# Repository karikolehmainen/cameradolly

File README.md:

# Camera Timelapse Dolly #
This camera dolly was born from desire to take moving timelapse videos in cold 
environment. Project has not evolved in features much since its conception 
during 2016 but in implementation much so. First implementation was using Adafruit
Motor HAT with NEMA17 stepper motors to move dolly and rotate camera head. Only new
feature is autamtec head alignment according to earth axis that has appeared 
since the first version. This is noe third revision. 
## Features ##
Summary of main high level features of the dolly
- Move camera along rail using timing belt
- End stops to detect end of rail
- Rotate camera 360° 
- Provide 8V power for camera (necessary in freezing conditions)
- Have lens heating element with temperature sensor
- Align camera rotation axis with earth axis for star tracking
- Control camera via USB interface
- Mobile app controls and 3G/4G connectivity

## Changes and rationale ##
Major change has been to ditch stepper motors in favour of DC motors. Main reason
behind the change was to enable star tracking and loooong exposures (like minutes
not seconds) as well as preserve energy. 
Also full size raspberry pi has been changes to Zero for more compact construction
and slightly less power consumption. Main drawback of this is the loss of 4G 
connectivity.

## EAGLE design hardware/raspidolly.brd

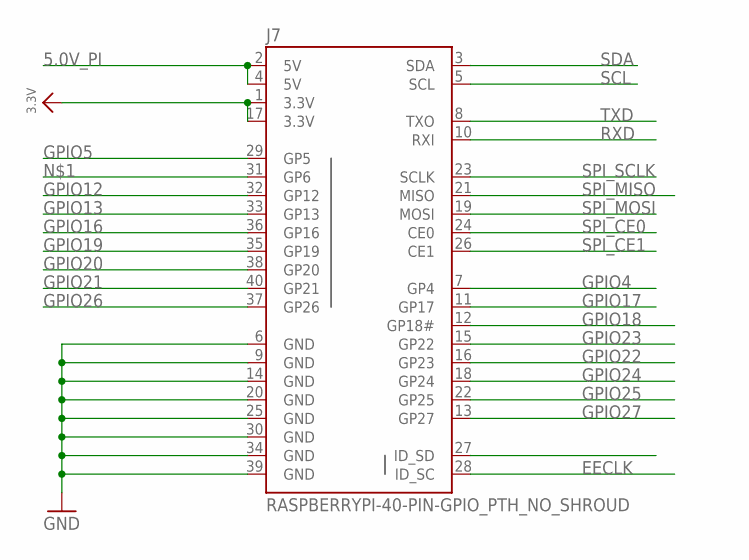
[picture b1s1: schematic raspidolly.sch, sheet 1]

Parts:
J7: RASPBERRYPI-40-PIN-GPIO_PTH_NO_SHROUD; 2X20

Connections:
3.3V: J7.1 (3.3V), J7.17 (3.3V); also elsewhere on the board
5.0V_PI: J7.2 (5V), J7.4 (5V); also elsewhere on the board
EECLK: J7.28 (ID_SC)
EEDATA: J7.27 (ID_SD)
GND: J7.6 (GND), J7.9 (GND), J7.14 (GND), J7.20 (GND), J7.25 (GND), J7.30 (GND), J7.34 (GND), J7.39 (GND); also elsewhere on the board
GPIO4: J7.7 (GP4); also elsewhere on the board
GPIO5: J7.29 (GP5)
GPIO12: J7.32 (GP12); also elsewhere on the board
GPIO13: J7.33 (GP13); also elsewhere on the board
GPIO16: J7.36 (GP16); also elsewhere on the board
GPIO17: J7.11 (GP17); also elsewhere on the board
GPIO18: J7.12 (GP18#); also elsewhere on the board
GPIO19: J7.35 (GP19); also elsewhere on the board
GPIO20: J7.38 (GP20); also elsewhere on the board
GPIO21: J7.40 (GP21); also elsewhere on the board
GPIO22: J7.15 (GP22)
GPIO23: J7.16 (GP23)
GPIO24: J7.18 (GP24)
GPIO25: J7.22 (GP25); also elsewhere on the board
GPIO26: J7.37 (GP26); also elsewhere on the board
GPIO27: J7.13 (GP27); also elsewhere on the board
RXD: J7.10 (RXI); also elsewhere on the board
SCL: J7.5 (SCL); also elsewhere on the board
SDA: J7.3 (SDA); also elsewhere on the board
SPI_CE0: J7.24 (CE0)
SPI_CE1: J7.26 (CE1)
SPI_MISO: J7.21 (MISO)
SPI_MOSI: J7.19 (MOSI)
SPI_SCLK: J7.23 (SCLK)
TXD: J7.8 (TXO); also elsewhere on the board

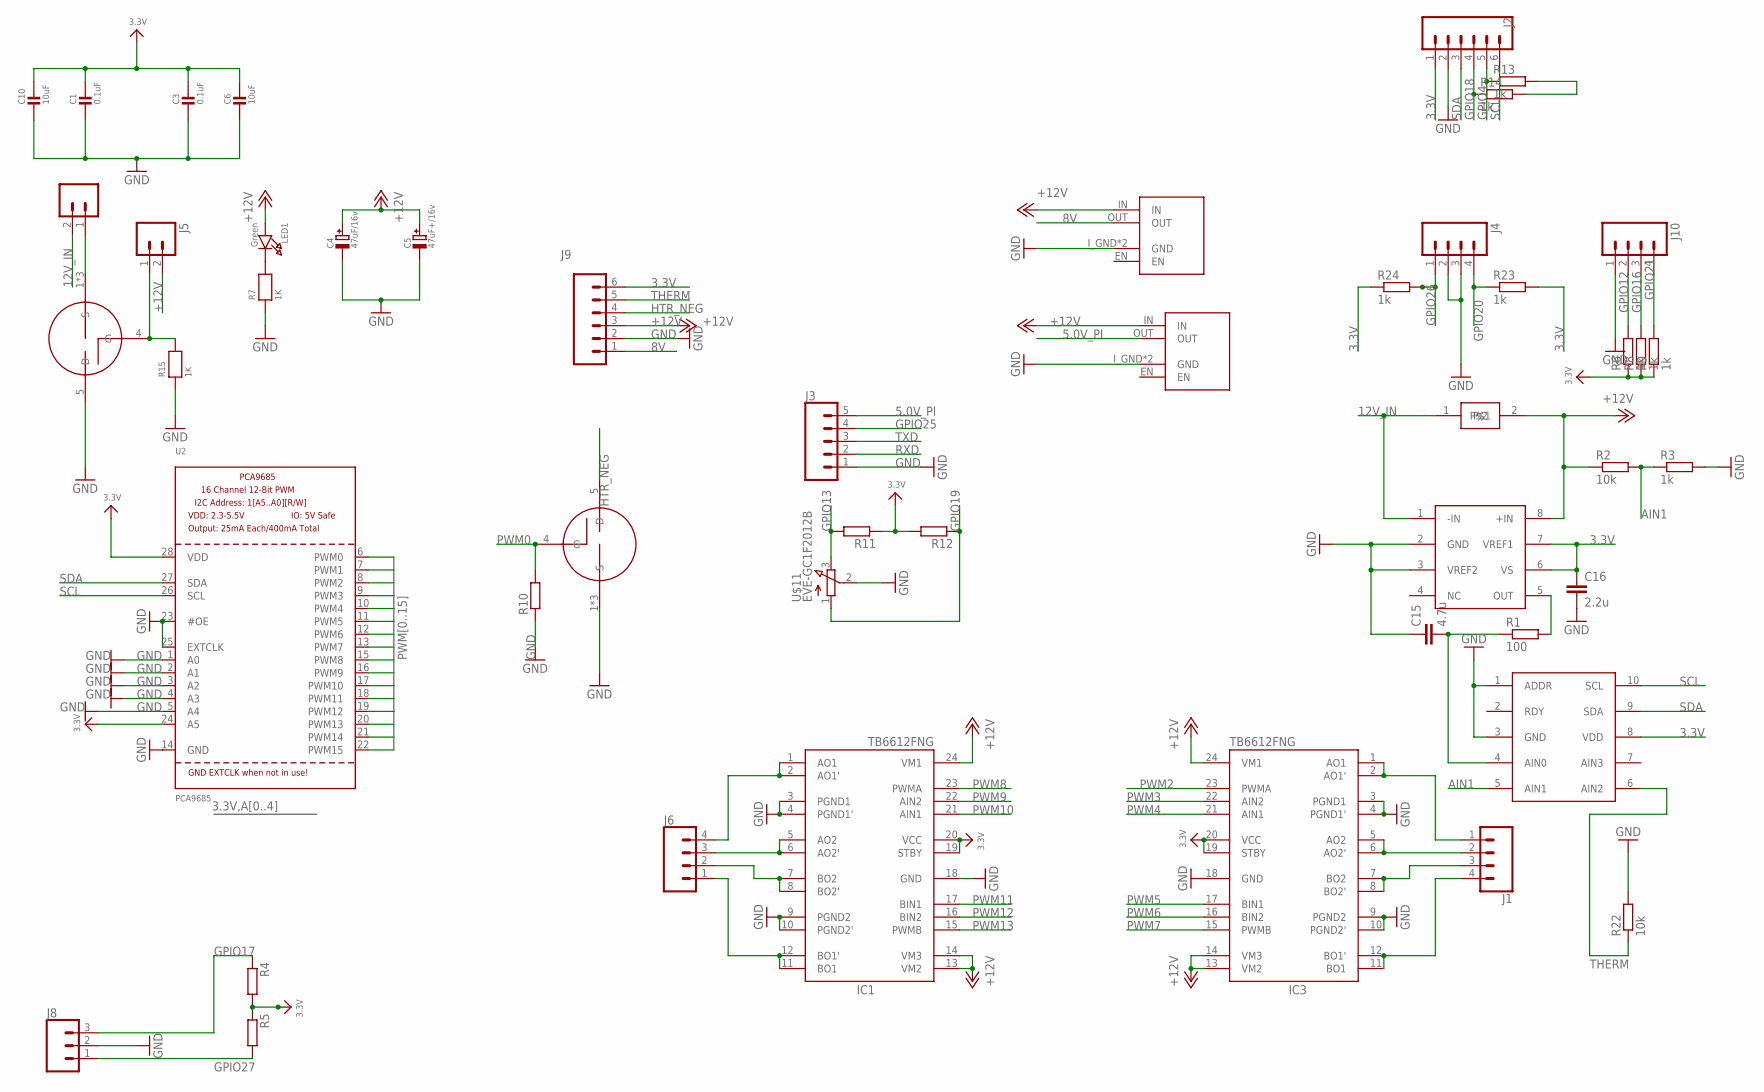
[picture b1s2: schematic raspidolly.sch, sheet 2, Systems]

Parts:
C1, C3: 0.1uF; 0805-NO
C4: 47uF/16v; PANASONIC_C
C5: 47uF+/16v; PANASONIC_C
C6, C10: 10uF; 0805-NO
C15: 4.7u; C0805
C16: 2.2u; C0805
IC1, IC3: TB6612FNG; SSOP24
J1, J6: CONN_04; 1X04
J2, J9: CONN_061.27MM; 1X06_1.27MM
J3: CONN_051.27MM; 1X05_1.27MM
J4, J10: M04JST; 1X04-1.5MM_JST
J5: M02PTH; 1X02
J8: CONN_03JST-PTH-VERT; JST-3-PTH-VERT
LED1: Green; CHIPLED_0805_NOOUTLINE
MPOWER: CONN_02; 1X02
R1: 100; R0805
R2, R22: 10k; R0805
R3, R6, R8, R9, R13, R14, R23, R24: 1k; R0805
R4, R5, R10, R11, R12: R-EU_R0805; R0805
R7, R15: 1K; 0805-NO
U2: PCA9685; TSSOP28
U$5, U$6: BUK9M; LFPAK33
U$8, U$10: UFH-BUCK
U$11: EVE-GC1F2012B; EVE
U$14: AD8418; MSOP08
U$15: ADS1015; VSSOP10
U$17: RESISTOR; 3921

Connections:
3.3V: C1.1, C3.1, C6.1, C10.1, C16.1, IC1.19 (STBY), IC1.20 (VCC), IC3.19 (STBY), IC3.20 (VCC), J2.1, J9.6, R4.2, R5.1, R6.1, R8.1, R9.1, R11.1, R12.2, R13.2, R14.2, R23.2, R24.1, U2.24 (A5), U2.28 (VDD), U$14.6 (VS), U$14.7 (VREF1), U$15.8 (VDD); also elsewhere on the board
5.0V_PI: J3.5, U$10.OUT; also elsewhere on the board
8V: J9.1, U$8.OUT
12V_IN: MPOWER.2, U$14.1 (-IN), U$17.1
+12V: C4.+, C5.+, IC1.13 (VM2), IC1.14 (VM3), IC1.24 (VM1), IC3.13 (VM2), IC3.14 (VM3), IC3.24 (VM1), J5.2, J9.3, LED1.A, R2.1, U$8.IN, U$10.IN, U$14.8 (+IN), U$17.2
AIN1: R2.2, R3.1, U$15.5 (AIN1)
GND: C1.2, C3.2, C4.-, C5.-, C6.2, C10.2, C15.1, C16.2, IC1.3 (PGND1), IC1.4 (PGND1'), IC1.9 (PGND2), IC1.10 (PGND2'), IC1.18 (GND), IC3.3 (PGND1), IC3.4 (PGND1'), IC3.9 (PGND2), IC3.10 (PGND2'), IC3.18 (GND), J2.2, J3.1, J4.2, J4.3, J8.2, J9.2, J10.1, R3.2, R7.1, R10.1, R15.1, R22.2, U2.1 (A0), U2.2 (A1), U2.3 (A2), U2.4 (A3), U2.5 (A4), U2.14 (GND), U2.23 (#OE), U2.25 (EXTCLK), U$5.1 (S), U$5.2 (S), U$5.3 (S), U$6.5 (D), U$8.I_GND (GND), U$8.O_GND (GND), U$10.I_GND (GND), U$10.O_GND (GND), U$11.2 (COM), U$14.2 (GND), U$14.3 (VREF2), U$15.1 (ADDR), U$15.3 (GND); also elsewhere on the board
GPIO4: J2.5, R13.1; also elsewhere on the board
GPIO12: J10.2, R6.2; also elsewhere on the board
GPIO13: R11.2, U$11.3 (B); also elsewhere on the board
GPIO16: J10.3, R8.2; also elsewhere on the board
GPIO17: J8.3, R4.1; also elsewhere on the board
GPIO18: J2.4, R14.1; also elsewhere on the board
GPIO19: R12.1, U$11.1 (A); also elsewhere on the board
GPIO20: J4.4, R23.1; also elsewhere on the board
GPIO21: J10.4, R9.2; also elsewhere on the board
GPIO25: J3.4; also elsewhere on the board
GPIO26: J4.1, R24.2; also elsewhere on the board
GPIO27: J8.1, R5.2; also elsewhere on the board
HTR_NEG: J9.4, U$5.5 (D)
unnamed: MPOWER.1, U$6.1 (S), U$6.2 (S), U$6.3 (S)
unnamed: IC1.1 (AO1), IC1.2 (AO1'), J6.4
unnamed: IC1.5 (AO2), IC1.6 (AO2'), J6.3
unnamed: IC1.7 (BO2), IC1.8 (BO2'), J6.2
unnamed: IC1.11 (BO1), IC1.12 (BO1'), J6.1
unnamed: J5.1, R15.2, U$6.4 (G)
unnamed: IC3.1 (AO1), IC3.2 (AO1'), J1.1
unnamed: IC3.5 (AO2), IC3.6 (AO2'), J1.2
unnamed: IC3.7 (BO2), IC3.8 (BO2'), J1.3
unnamed: R1.2, U$14.5 (OUT)
unnamed: IC3.11 (BO1), IC3.12 (BO1'), J1.4
unnamed: C15.2, R1.1, U$15.4 (AIN0)
unnamed: LED1.C, R7.2
PWM0: R10.2, U2.6 (PWM0), U$5.4 (G)
PWM1: U2.7 (PWM1)
PWM2: IC3.23 (PWMA), U2.8 (PWM2)
PWM3: IC3.22 (AIN2), U2.9 (PWM3)
PWM4: IC3.21 (AIN1), U2.10 (PWM4)
PWM5: IC3.17 (BIN1), U2.11 (PWM5)
PWM6: IC3.16 (BIN2), U2.12 (PWM6)
PWM7: IC3.15 (PWMB), U2.13 (PWM7)
PWM8: IC1.23 (PWMA), U2.15 (PWM8)
PWM9: IC1.22 (AIN2), U2.16 (PWM9)
PWM10: IC1.21 (AIN1), U2.17 (PWM10)
PWM11: IC1.17 (BIN1), U2.18 (PWM11)
PWM12: IC1.16 (BIN2), U2.19 (PWM12)
PWM13: IC1.15 (PWMB), U2.20 (PWM13)
PWM14: U2.21 (PWM14)
PWM15: U2.22 (PWM15)
RXD: J3.2; also elsewhere on the board
SCL: J2.6, U2.26 (SCL), U$15.10 (SCL); also elsewhere on the board
SDA: J2.3, U2.27 (SDA), U$15.9 (SDA); also elsewhere on the board
THERM: J9.5, R22.1, U$15.6 (AIN2)
TXD: J3.3; also elsewhere on the board

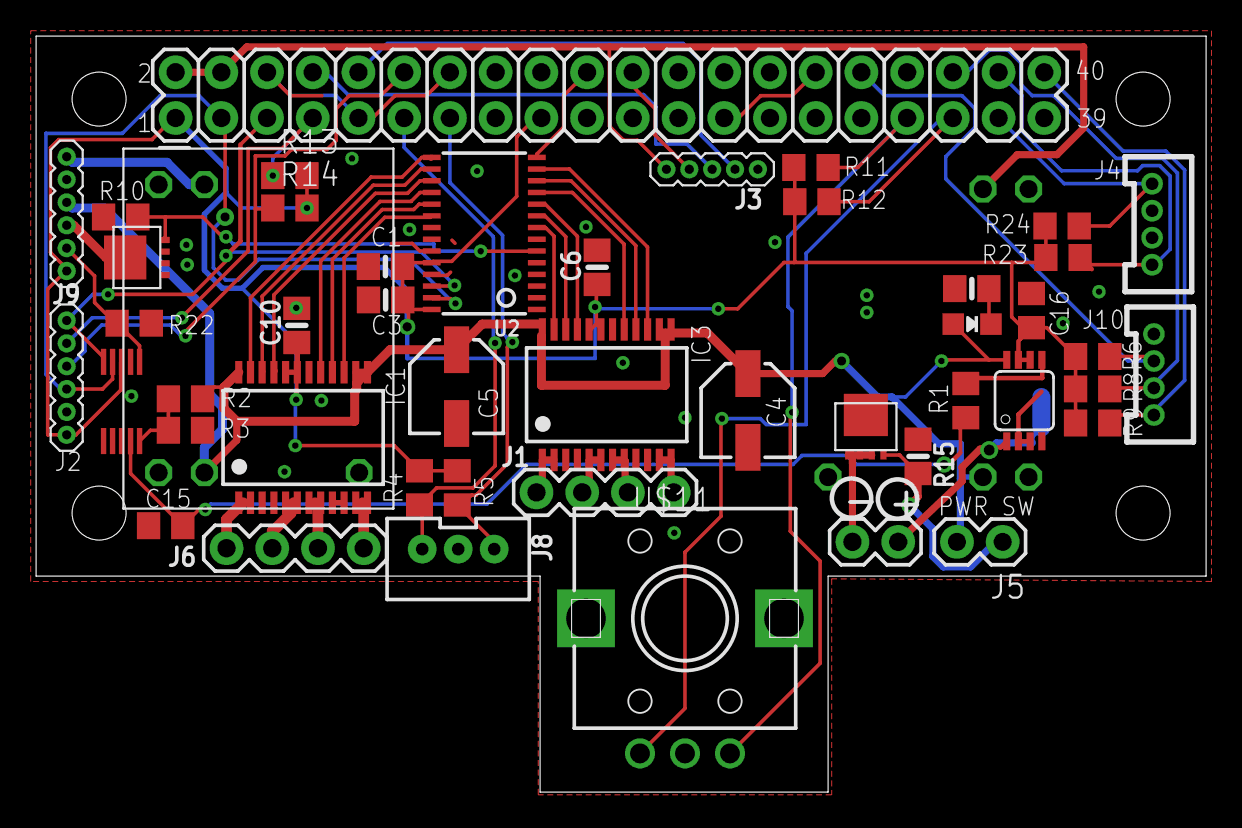
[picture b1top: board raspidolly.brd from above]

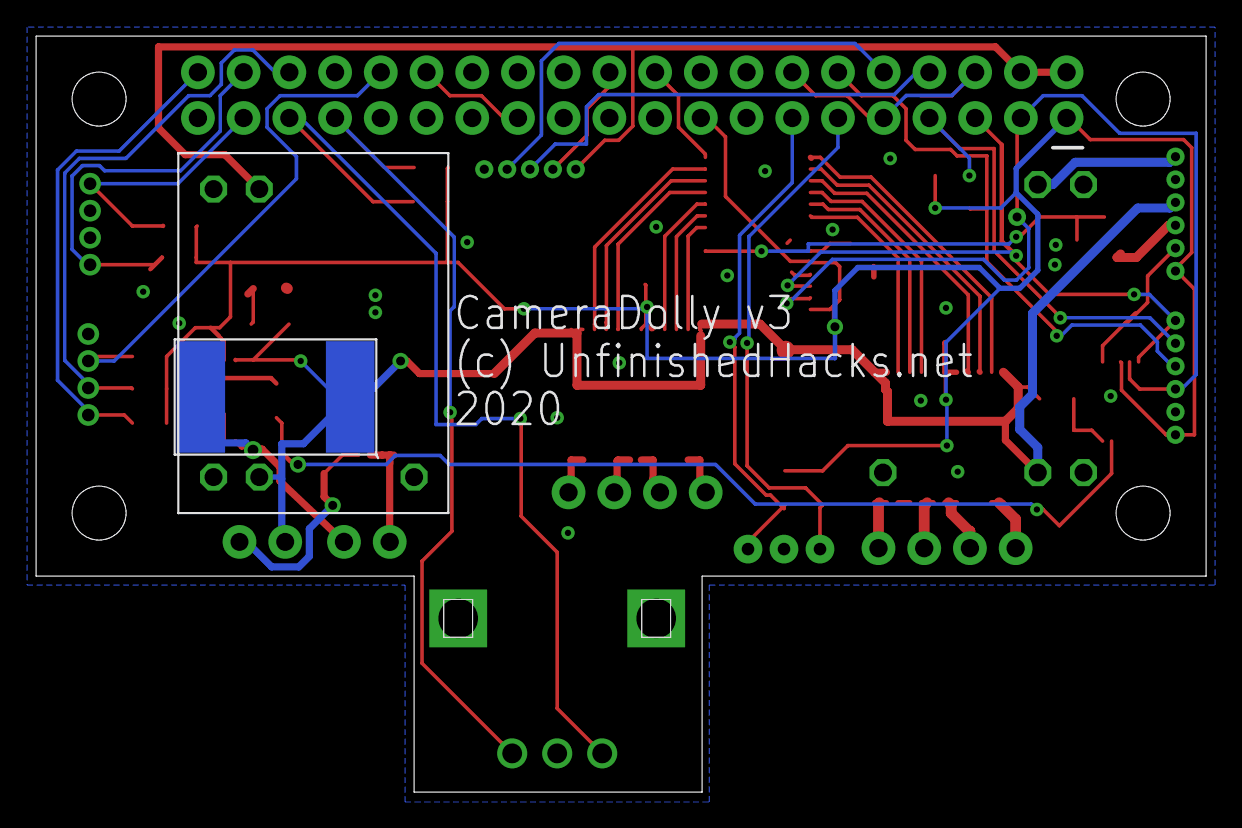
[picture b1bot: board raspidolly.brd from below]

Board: 2 copper layers, 65.0 x 42.0 mm, 49 parts (2 on the bottom side), 51 nets.

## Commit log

2021-11-27 added hw design files
2021-11-27 added READMEs
2021-11-29 some updates
2021-11-29 ADC reading mods
2021-11-29 ADC dividers for volt&curr
2021-11-29 added MQTT message ro readme
2021-11-29 dolly moving works
2021-11-29 some head updates
2021-11-29 stated speed sensing logic
2021-11-29 speed measurement working
2021-12-01 linear motor and end stops tested
2021-12-02 added STL files for track ends
2021-12-04 some fixes
2021-12-08 track measuring and head rotating works (possible HW problems with ADC)
2021-12-08 fixed bug in config file
2021-12-08 some bug fixes & earth axis leveling now working
2021-12-13 updated few MQTT messages
2021-12-13 added iOS app stub
2021-12-13 updated iOS app stub with MQTT Client
2021-12-16 iOS app now minum viable product so to spead. start, stop and gotostart works
2021-12-17 iOS app now have most important functions working
2021-12-17 refined some status messagign and head rotation
2021-12-28 some updates to functions to get around HW bugs

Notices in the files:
parts and their libraries:
microbuilder: This work is placed in the public domain, and may be freely used for commercial and non-commercial work with the following conditions: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
SparkFun-Connectors: Licensing: Creative Commons ShareAlike 4.0 International - https://creativecommons.org/licenses/by-sa/4.0
